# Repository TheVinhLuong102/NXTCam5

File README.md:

***NXTCam5 (Machine Vision for NXT and EV3)***

NXTCam5 is an open-source machine vision module based on OpenMV.

Video of an EV3 Robot capturing a video: 
https://www.youtube.com/watch?v=-306g3WNhL8

For more information, please visit (http://www.mindsensors.com/pages/317)

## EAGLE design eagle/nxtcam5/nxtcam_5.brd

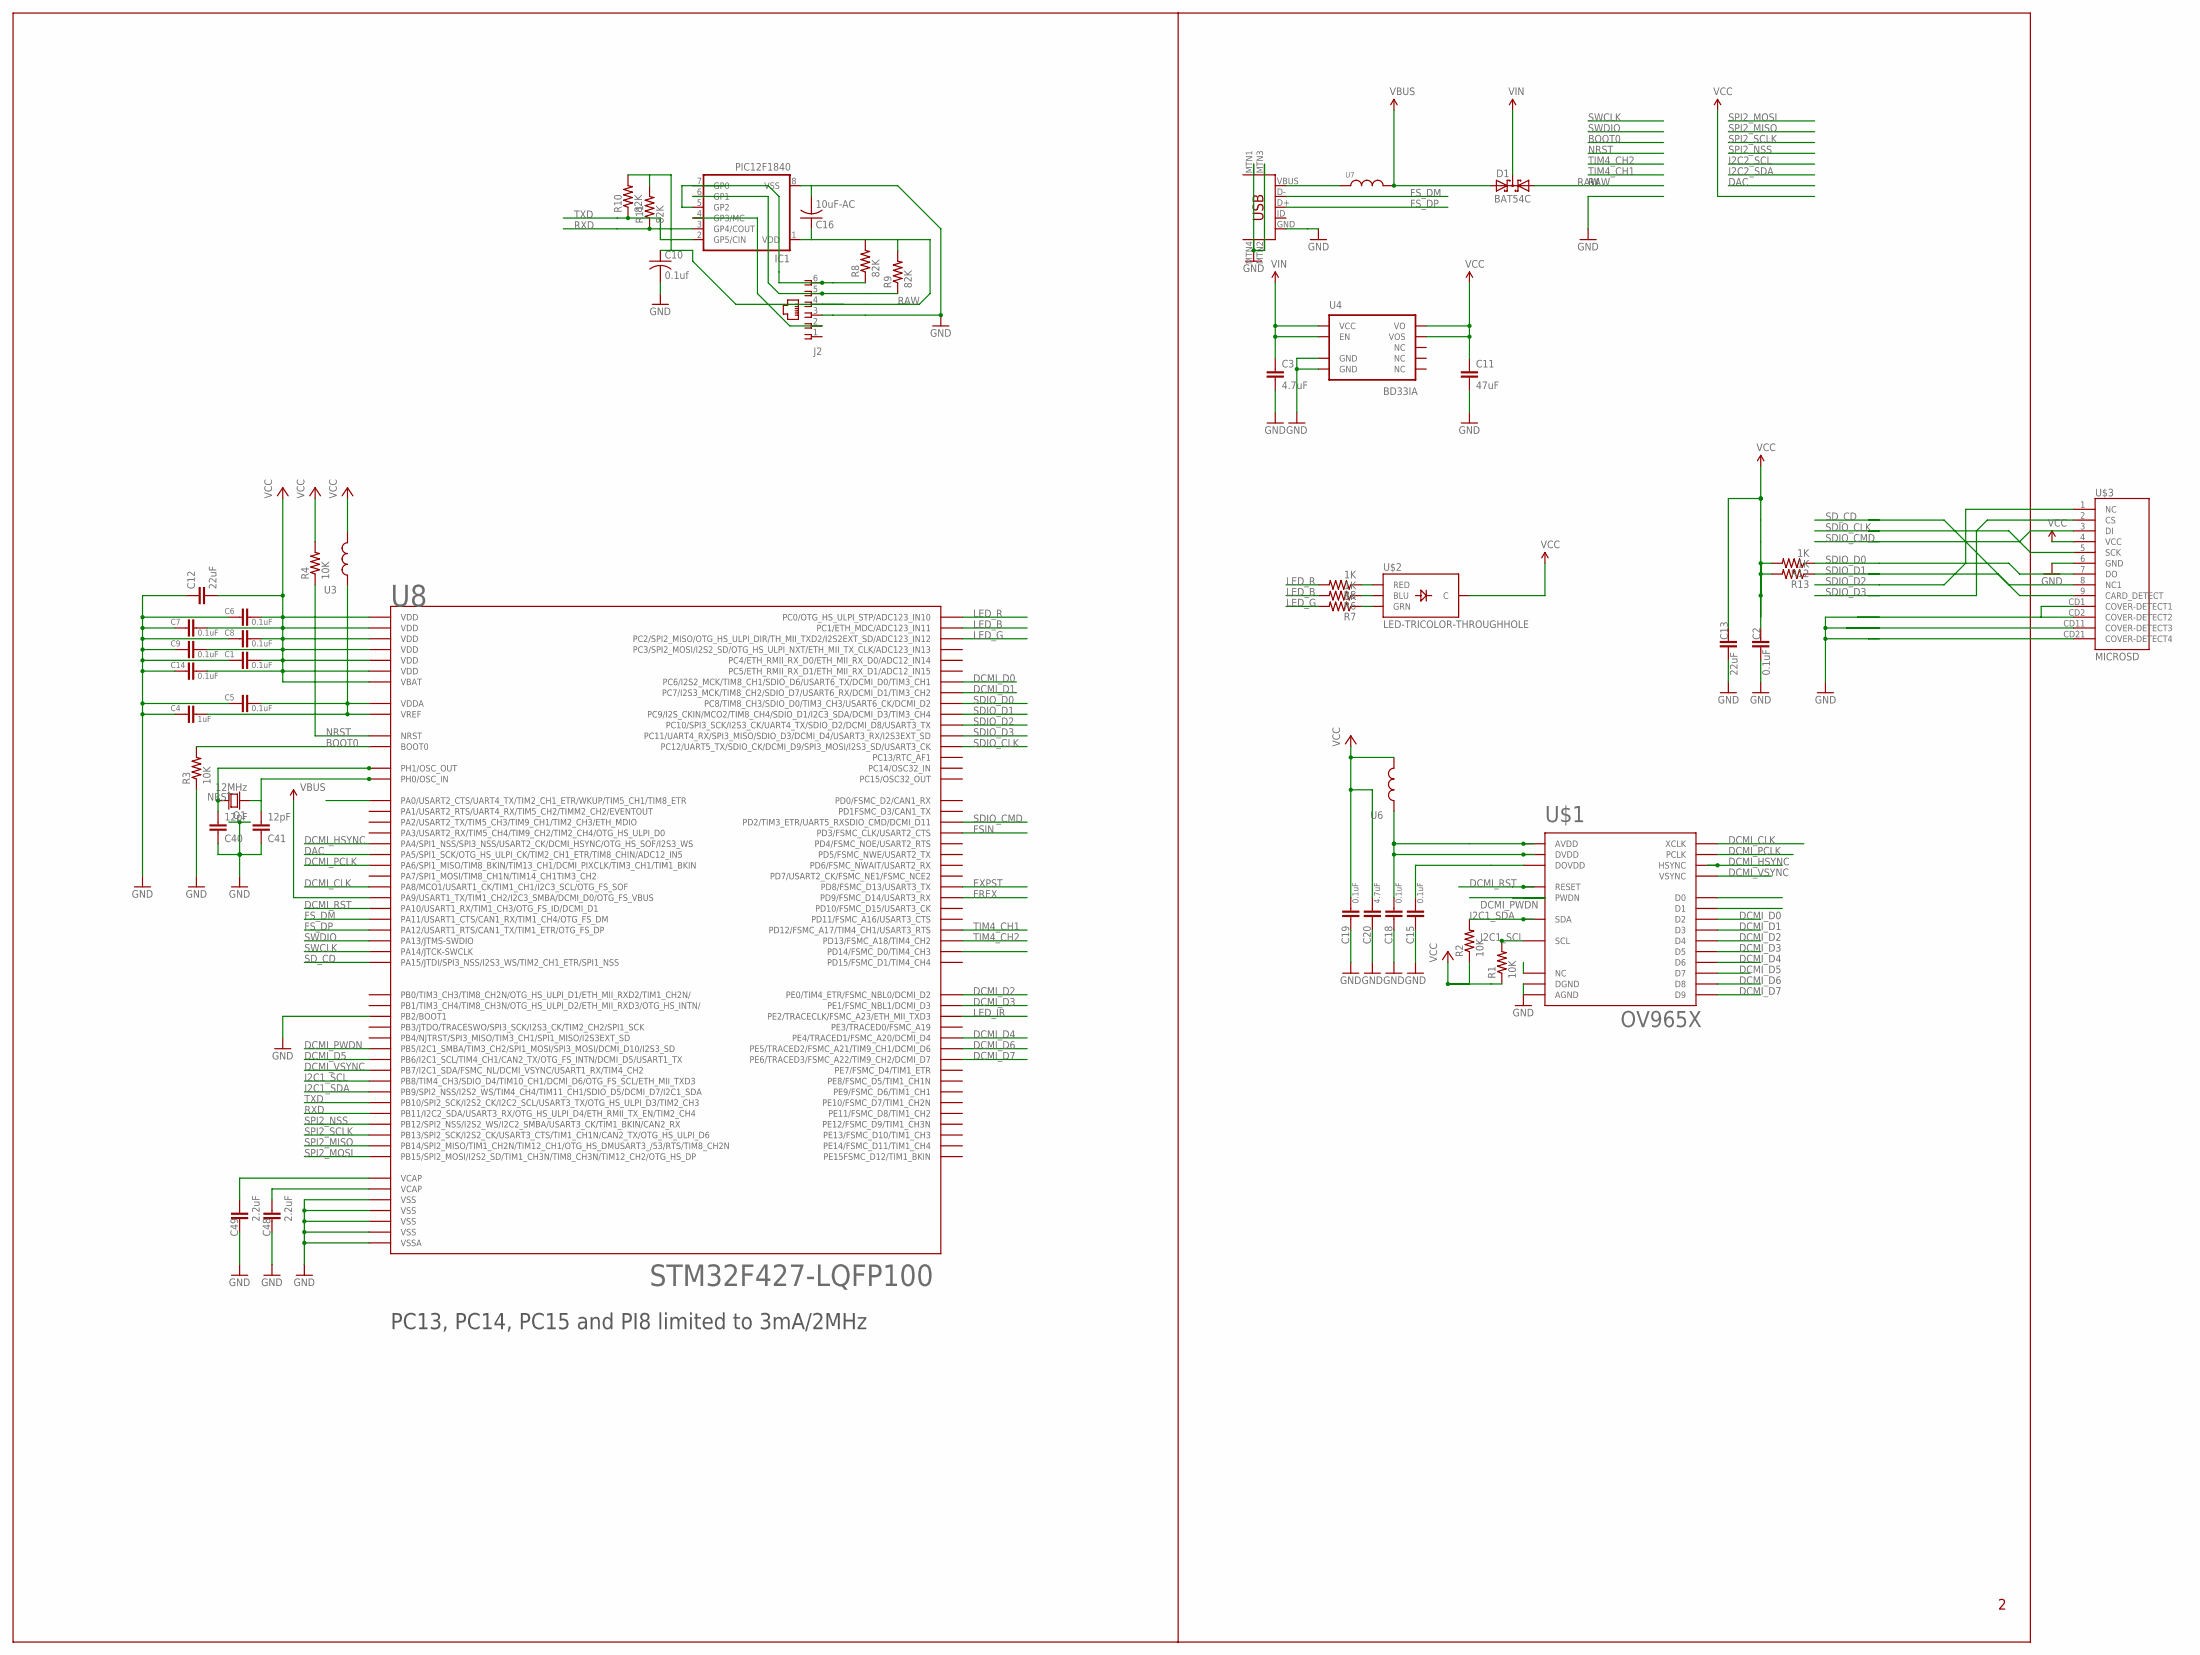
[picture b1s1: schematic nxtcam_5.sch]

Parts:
C1, C2, C5, C6, C7, C8, C9, C14, C15, C18, C19: 0.1uF; 0603-CAP
C3, C20: 4.7uF; 0603-CAP
C4: 1uF; 0603-CAP
C10: 0.1uf; C0603K
C11: 47uF; 1206
C12, C13: 22uF; 0805
C16: 10uF-AC; C1206K
C40, C41: 12pF; 0603-CAP
C48, C49: 2.2uF; 0603-CAP
D1: BAT54C; SOT23
IC1: PIC12F1840; SOIC08
J2: NXTCONN0
Q1: 12MHz; TXC-SMD-50X32
R1, R2, R3, R4: 10K; 0603-RES
R5, R6, R7, R12, R13: 1K; 0603-RES
R8, R9, R10, R11: 82K; R0603
U3, U6, U7: INDUCTOR0603; 0603
U4: BD33IA; HTSOP-J8
U8: STM32F427-LQFP100; LQFP100
U$1: OV965X
U$2: LED-TRICOLOR-THROUGHHOLE; LED_TRICOLOR_THROUGHHOLE_SM
U$3: MICROSD; MICROSD_CN
U$4: USB-MINIBTH; USB-MINIB-ALIGNPINS

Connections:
BOOT0: R3.2, U8.94 (BOOT0)
DAC: U8.30 (PA5/SPI1_SCK/OTG_HS_ULPI_CK/TIM2_CH1_ET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)
DCMI_CLK: U8.67 (PA8/MCO1/USART1_CK/TIM1_CH1/I2C3_SCL/OT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), U$1.P$13 (XCLK)
DCMI_D0: U8.63 (PC6/I2S2_MCK/TIM8_CH1/SDIO_D6/USART6_TX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), U$1.P$19 (D2)
DCMI_D1: U8.64 (PC7/I2S3_MCK/TIM8_CH2/SDIO_D7/USART6_RX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), U$1.P$21 (D3)
DCMI_D2: U8.97 (PE0/TIM4_ETR/FSMC_NBL0/DCMI_D2), U$1.P$22 (D4)
DCMI_D3: U8.98 (PE1/FSMC_NBL1/DCMI_D3), U$1.P$20 (D5)
DCMI_D4: U8.3 (PE4/TRACED1/FSMC_A20/DCMI_D4), U$1.P$18 (D6)
DCMI_D5: U8.92 (PB6/I2C1_SCL/TIM4_CH1/CAN2_TX/OTG_FS_IN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), U$1.P$16 (D7)
DCMI_D6: U8.4 (PE5/TRACED2/FSMC_A21/TIM9_CH1/DCMI_D6), U$1.P$14 (D8)
DCMI_D7: U8.5 (PE6/TRACED3/FSMC_A22/TIM9_CH2/DCMI_D7), U$1.P$12 (D9)
DCMI_HSYNC: U8.29 (PA4/SPI1_NSS/SPI3_NSS/USART2_CK/DCMI_HS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), U$1.P$9 (HSYNC)
DCMI_PCLK: U8.31 (PA6/SPI1_MISO/TIM8_BKIN/TIM13_CH1/DCMI_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), U$1.P$17 (PCLK)
DCMI_PWDN: U8.91 (PB5/I2C1_SMBA/TIM3_CH2/SPI1_MOSI/SPI3_M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), U$1.P$8 (PWDN)
DCMI_RST: U8.69 (PA10/USART1_RX/TIM1_CH3/OTG_FS_ID/DCMI_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), U$1.P$6 (RESET)
DCMI_VSYNC: U8.93 (PB7/I2C1_SDA/FSMC_NL/DCMI_VSYNC/USART1_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), U$1.P$7 (VSYNC)
EXPST: U8.55 (PD8/FSMC_D13/USART3_TX)
FREX: U8.56 (PD9/FSMC_D14/USART3_RX)
FSIN: U8.84 (PD3/FSMC_CLK/USART2_CTS)
FS_DM: U8.70 (PA11/USART1_CTS/CAN1_RX/TIM1_CH4/OTG_FS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), U$4.D-
FS_DP: U8.71 (PA12/USART1_RTS/CAN1_TX/TIM1_ETR/OTG_FS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), U$4.D+
GND: C1.2, C2.2, C3.2, C4.2, C5.2, C6.2, C7.2, C8.2, C9.2, C10.2, C11.2, C12.1, C13.2, C14.2, C15.2, C16.2, C18.2, C19.2, C20.2, C40.1, C41.1, C48.2, C49.2, IC1.8 (VSS), J2.3, R3.1, U4.3 (GND), U4.P$1 (GND), U8.10 (VSS), U8.20 (VSSA), U8.27 (VSS), U8.37 (PB2/BOOT1), U8.74 (VSS), U8.99 (VSS), U$1.P$2 (AGND), U$1.P$15 (DGND), U$3.6 (GND), U$3.CD1 (COVER-DETECT1), U$3.CD2 (COVER-DETECT2), U$3.CD11 (COVER-DETECT3), U$3.CD21 (COVER-DETECT4), U$4.GND, U$4.MTN1 (MTN2), U$4.MTN2 (MTN3), U$4.MTN3 (MTN1), U$4.MTN4
I2C1_SCL: R1.2, U8.95 (PB8/TIM4_CH3/SDIO_D4/TIM10_CH1/DCMI_D6/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), U$1.P$5 (SCL)
I2C1_SDA: R2.2, U8.96 (PB9/SPI2_NSS/I2S2_WS/TIM4_CH4/TIM11_CH1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), U$1.P$3 (SDA)
LED_B: R6.2, U8.16 (PC1/ETH_MDC/ADC123_IN11)
LED_G: R7.2, U8.17 (PC2/SPI2_MISO/OTG_HS_ULPI_DIR/TH_MII_TX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)
LED_IR: U8.1 (PE2/TRACECLK/FSMC_A23/ETH_MII_TXD3)
LED_R: R5.2, U8.15 (PC0/OTG_HS_ULPI_STP/ADC123_IN10)
unnamed: C40.2, Q1.P$2, U8.13 (PH1/OSC_OUT)
unnamed: IC1.5 (GP2), IC1.7 (GP0), J2.6, R8.1
unnamed: C41.2, Q1.P$1, U8.12 (PH0/OSC_IN)
unnamed: IC1.6 (GP1), J2.5, R9.1
unnamed: IC1.4 (GP3/MC), J2.2
unnamed: C4.1, C5.1, U3.1, U8.21 (VREF), U8.22 (VDDA)
unnamed: C18.1, U6.1, U$1.P$4 (AVDD), U$1.P$10 (DVDD)
unnamed: R5.1, U$2.RED
unnamed: U7.1, U$4.VBUS
unnamed: R6.1, U$2.BLU
unnamed: C15.1, U$1.P$11 (DOVDD)
unnamed: R7.1, U$2.GRN
NRST: R4.1, U8.14 (NRST)
RAW: C10.1, C16.1, D1.1 (A1), IC1.1 (VDD), J2.4, R8.2, R9.2, R10.2, R11.2
RXD: IC1.3 (GP4/COUT), R11.1, U8.48 (PB11/I2C2_SDA/USART3_RX/OTG_HS_ULPI_D4/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)
SDIO_CLK: U8.80 (PC12/UART5_TX/SDIO_CK/DCMI_D9/SPI3_MOSI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), U$3.5 (SCK)
SDIO_CMD: U8.83 (PD2/TIM3_ETR/UART5_RXSDIO_CMD/DCMI_D11), U$3.3 (DI)
SDIO_D0: R12.1, U8.65 (PC8/TIM8_CH3/SDIO_D0/TIM3_CH3/USART6_CK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), U$3.7 (DO)
SDIO_D1: R13.1, U8.66 (PC9/I2S_CKIN/MCO2/TIM8_CH4/SDIO_D1/I2C3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), U$3.8 (NC1)
SDIO_D2: U8.78 (PC10/SPI3_SCK/I2S3_CK/UART4_TX/SDIO_D2/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), U$3.1 (NC)
SDIO_D3: U8.79 (PC11/UART4_RX/SPI3_MISO/SDIO_D3/DCMI_D4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), U$3.2 (CS)
SD_CD: U8.77 (PA15/JTDI/SPI3_NSS/I2S3_WS/TIM2_CH1_ETR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), U$3.9 (CARD_DETECT)
SPI2_MISO: U8.53 (PB14/SPI2_MISO/TIM1_CH2N/TIM12_CH1/OTG_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)
SPI2_MOSI: U8.54 (PB15/SPI2_MOSI/I2S2_SD/TIM1_CH3N/TIM8_C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)
SPI2_NSS: U8.51 (PB12/SPI2_NSS/I2S2_WS/I2C2_SMBA/USART3_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)
SPI2_SCLK: U8.52 (PB13/SPI2_SCK/I2S2_CK/USART3_CTS/TIM1_C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)
SWCLK: U8.76 (PA14/JTCK-SWCLK)
SWDIO: U8.72 (PA13/JTMS-SWDIO)
TIM4_CH1: U8.59 (PD12/FSMC_A17/TIM4_CH1/USART3_RTS)
TIM4_CH2: U8.60 (PD13/FSMC_A18/TIM4_CH2)
TXD: IC1.2 (GP5/CIN), R10.1, U8.47 (PB10/SPI2_SCK/I2S2_CK/I2C2_SCL/USART3_T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)
VBUS: D1.2 (A2), U7.2, U8.68 (PA9/USART1_TX/TIM1_CH2/I2C3_SMBA/DCMI_D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)
VCAP1: C49.1, U8.49 (VCAP)
VCAP2: C48.1, U8.73 (VCAP)
VCC: C1.1, C2.1, C6.1, C7.1, C8.1, C9.1, C11.1, C12.2, C13.1, C14.1, C19.1, C20.1, R1.1, R2.1, R4.2, R12.2, R13.2, U3.2, U4.1 (VO), U4.2 (VOS), U6.2, U8.6 (VBAT), U8.11 (VDD), U8.19 (VDD), U8.28 (VDD), U8.50 (VDD), U8.75 (VDD), U8.100 (VDD), U$2.GND (C), U$3.4 (VCC)
VIN: C3.1, D1.3 (CC), U4.5 (EN), U4.8 (VCC)

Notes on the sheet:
PC13, PC14, PC15 and PI8 limited to 3mA/2MHz

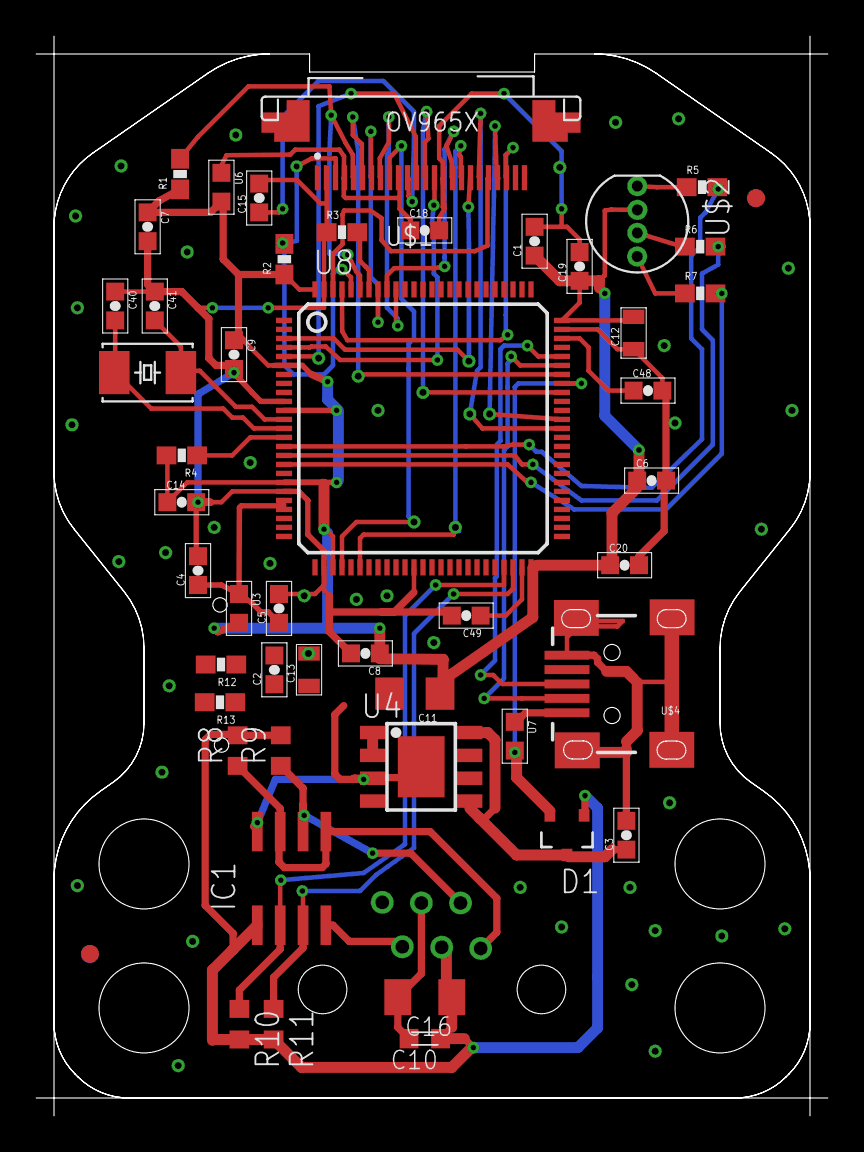
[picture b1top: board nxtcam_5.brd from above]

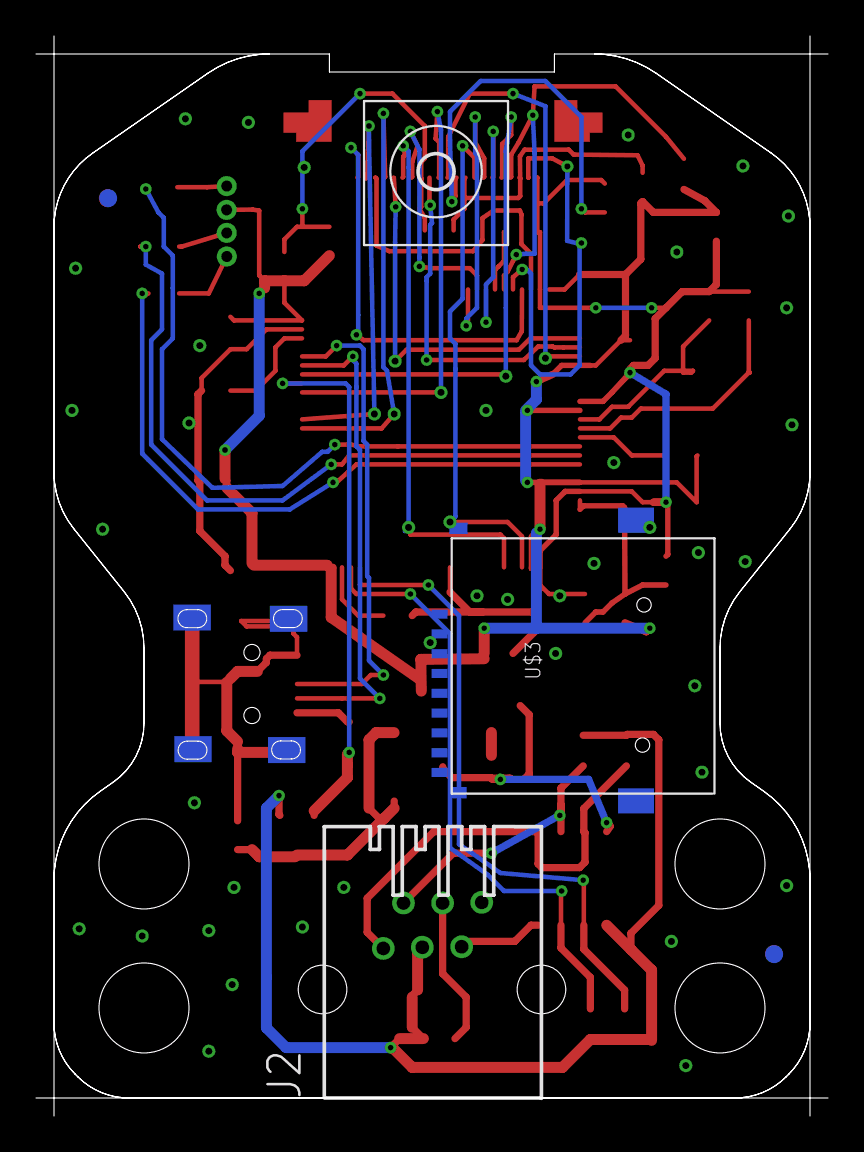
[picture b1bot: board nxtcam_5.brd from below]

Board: 2 copper layers, 44.0 x 60.0 mm, 53 parts (4 on the bottom side), 51 nets.

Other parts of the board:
GFID1, GFID2, GFID3, GFID4: Gfid1; VISION_REF10

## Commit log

2017-05-30 NXTCam5
2017-06-01 Add NXTCam5 schematic files

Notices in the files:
eagle/nxtcam5/nxtcam_5.sch:
Copyright (c) 2013 Ibrahim Abd Elkader
This work is licensed under the Creative Commons Attribution-ShareAlike 3.0 License.
To view a copy of this license, visit http://creativecommons.org/licenses/by-sa/3.0
